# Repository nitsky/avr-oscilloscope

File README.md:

# avr-oscilloscope

Pushing the ATMega328 to its limit: A 150 ksps oscilloscope with edge triggering written in AVR C.

## ADC
The ADC is configured to operate in free running mode, which means it samples continuously and calls an interrupt when each new sample is ready, which is once every 13.5 ADC clock cycles. The top ADC clock speed for 8-bit resolution is 4MHz, a prescaler of 4 with a 16MHz processor clock. Here is the code that configures the ADC and then functions to start and stop it.

```c
void init_adc()
{
    cbi(ADCSRA, ADEN); // disable adc
    cbi(ADCSRA, ADSC); // stop conversion

    cbi(ADMUX, REFS1); // choose AVcc with external cap
    sbi(ADMUX, REFS0); // for adc voltage reference
    sbi(ADMUX, ADLAR); // left adjust adc readings for 8 bit
    ADMUX |= ( 0 & 0x07 ); // choose analog 0 pin

    sbi(ADCSRA, ADATE); // enable auto trigger of adc
    sbi(ADCSRA, ADIE); // enable adc interrupt

    cbi(ADCSRA, ADPS2); // set prescaler to 4
    sbi(ADCSRA, ADPS1); //
    cbi(ADCSRA, ADPS0); //

    cbi(ADCSRB, ACME); // choose AIN1 for comparator

    cbi(ADCSRB, ADTS2); // choose free running mode
    cbi(ADCSRB, ADTS1); // for auto trigger adc
    cbi(ADCSRB, ADTS0);
}

void start_adc()
{
    sbi( ADCSRA, ADEN );
    sbi( ADCSRA, ADSC );
}

void stop_adc()
{
    cbi( ADCSRA, ADEN );
    cbi( ADCSRA, ADSC );
}
```

## Comparator

The comparator is configured without an interrupt because the comparator's value is read in the ADC interrupt.

```c
void init_comparator(void)
{
    cbi( ACSR, ACD ); // turn on comparator
    cbi( ACSR, ACBG ); // choose digital pin 7 for comparator
    cbi( ACSR, ACIE ); // disable interrupt

    cbi( ACSR, ACIC ); // disable input capture interrupt
}
```

## ADC Interrupt

The ADC interrupt implements a circular buffer of 1024 8-bit samples. At each interrupt it checks if the comparator has detected the input voltage above the trigger level eight consecutive times, a simple noise filter, then sets the stop_index which the interrupt will freeze itself at when it hits it, which is the current index plus half the buffer length, so that the trigger event is always at the center of the circular buffer.

```c
ISR(ADC_vect)
{
    adc_data[adc_counter] = ADCH; // read adc
    if (freeze) {
        freeze = false;
        stop_index = -1;
    } else if (adc_counter == stop_index) {
        freeze = true;
    } else if ( comp == 0 && (ACSR & (1 << ACO)) && stop_index < 0) {
        stop_index = ((adc_counter + (ADC_BUFFER_SIZE >> 1) ) & 0x03FF);
    }
    adc_counter = (( adc_counter + 1 ) & 0x03FF); // increment adc counter
    comp = (comp << 1); // push next comparator value
    comp += (ACSR & (1 << ACO));
}
```

## Trigger Level DAC

The ATMega328 does not have a DAC built-in to set the trigger level, but you can cheat by using PWM with a low-pass filter. For PWM frequency 490 Hz, I used a 100 kΩ resistor and 1 uF capacitor you can get reasonable delay and ripple in the mV range. Below is the code to use PWM on PD3. After this setup function the duty cycle can be changed by modifying the OCR2B register.

```c
void init_pwm()
{
    setOutput(DDRD, PORTD3);
    sbi(TCCR2A, COM2B1);
    sbi(TCCR2A, WGM20);
    sbi(TCCR2B, CS22);
    OCR2B = 128;
}
```

## UART

The UART is configured for 115200 baud. Here's the code to initialize it and then functions to send and receive characters.

```
#define BAUD 115200
#include <util/setbaud.h>

void uart_init() {
    UBRR0H = UBRRH_VALUE;
    UBRR0L = UBRRL_VALUE;

#if USE_2X
    UCSR0A |= _BV(U2X0);
#else
    UCSR0A &= ~(_BV(U2X0));
#endif

    UCSR0C = _BV(UCSZ01) | _BV(UCSZ00); // 8 bit
    UCSR0B = _BV(RXEN0) | _BV(TXEN0); // enable rx and tx
}

void uart_putchar(char c) {
    loop_until_bit_is_set(UCSR0A, UDRE0); // wait until reg empty
    UDR0 = c;
}

char uart_getchar() {
    loop_until_bit_is_set(UCSR0A, RXC0); // wait for byte
    return UDR0;
}
```

## Signal Conditioning

Below is the input signal conditioning circuit. The ADC operates from 0V to 5V, so the circuit uses an op-amp to scale and offset an incoming signal from -10V to 10V to 0V to 5V. It does this with a divide by four voltage divider and then a voltage adder with a 2.5V input from a voltage divider. All resistors in the schematic are 10kΩ except for R11 with is 1 MΩ to make the scope appear as a high impedence to whatever circuit it is measuring.

## Results

[Watch Video](https://vimeo.com/80199995)

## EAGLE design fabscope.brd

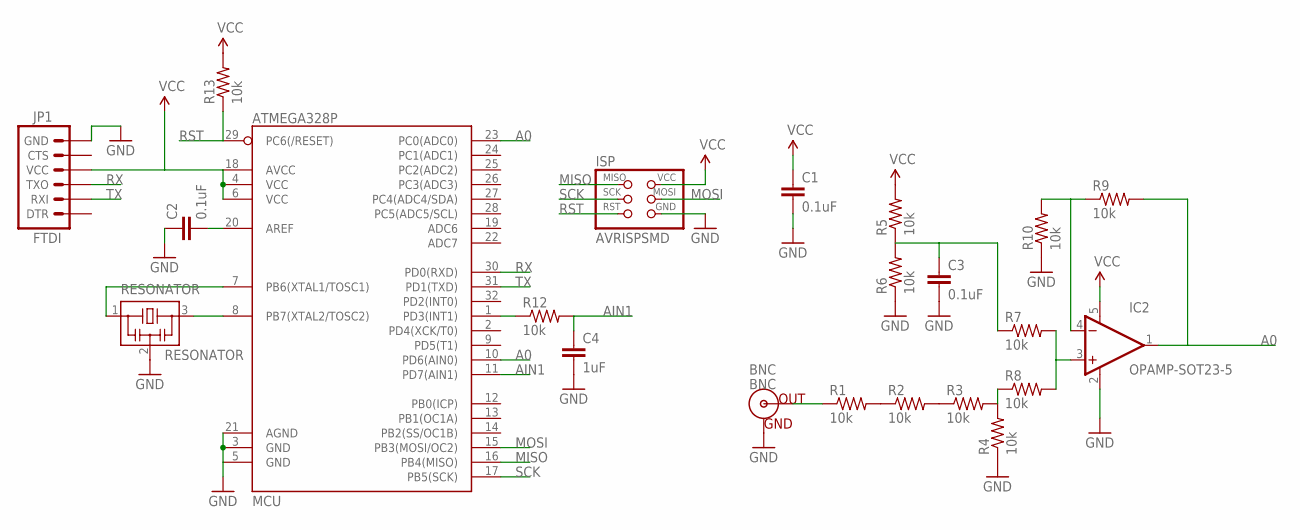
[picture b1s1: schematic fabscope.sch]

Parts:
BNC: BNC
C1, C2, C3: 0.1uF; C1206FAB
C4: 1uF; C1206FAB
IC2: OPAMP-SOT23-5; SOT23-5
ISP: AVRISPSMD; 2X3SMD
JP1: FTDI; FTDI-SMD
MCU: ATMEGA328P; TQFP32-08
R1, R2, R3, R4, R5, R6, R7, R8, R9, R10, R12, R13: 10k; R1206FAB
RESONATOR: RESONATOR; EFOBM

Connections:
A0: IC2.1 (OUT), MCU.10 (PD6(AIN0)), MCU.23 (PC0(ADC0)), R9.2
AIN1: C4.1, MCU.11 (PD7(AIN1)), R12.2
GND: BNC.GND, C1.2, C2.1, C3.2, C4.2, IC2.2 (V-), ISP.6 (GND), JP1.6 (GND), MCU.3 (GND), MCU.5 (GND), MCU.21 (AGND), R4.1, R6.1, R10.1, RESONATOR.2
MISO: ISP.1 (MISO), MCU.16 (PB4(MISO))
MOSI: ISP.4 (MOSI), MCU.15 (PB3(MOSI/OC2))
unnamed: MCU.7 (PB6(XTAL1/TOSC1)), RESONATOR.1
unnamed: MCU.8 (PB7(XTAL2/TOSC2)), RESONATOR.3
unnamed: BNC.S (OUT), R1.1
unnamed: C2.2, MCU.20 (AREF)
unnamed: R1.2, R2.1
unnamed: R2.2, R3.1
unnamed: R3.2, R4.2, R8.1
unnamed: C3.1, R5.1, R6.2, R7.1
unnamed: IC2.3 (+IN), R7.2, R8.2
unnamed: IC2.4 (-IN), R9.1, R10.2
unnamed: MCU.1 (PD3(INT1)), R12.1
RST: ISP.5 (RST), MCU.29 (PC6(/RESET)), R13.1
RX: JP1.3 (TXO), MCU.30 (PD0(RXD))
SCK: ISP.3 (SCK), MCU.17 (PB5(SCK))
TX: JP1.2 (RXI), MCU.31 (PD1(TXD))
VCC: C1.1, IC2.5 (V+), ISP.2 (VCC), JP1.4 (VCC), MCU.4 (VCC), MCU.6 (VCC), MCU.18 (AVCC), R5.2, R13.2

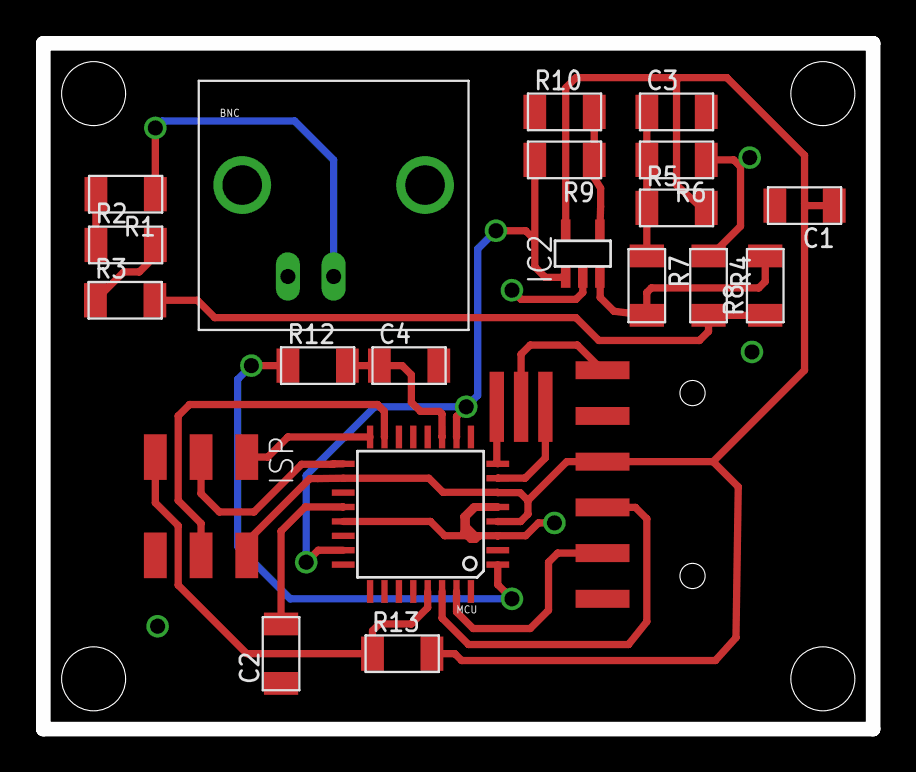
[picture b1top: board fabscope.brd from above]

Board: 2 copper layers, 46.1 x 38.1 mm, 22 parts (0 on the bottom side), 21 nets.

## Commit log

2013-11-24 initial import
2014-01-15 modified board and makefile
2014-01-15 removed old file
2014-01-15 fixes and fuses
2014-01-16 removed unused code
2014-04-02 rename
2016-01-25 add photos
2016-01-25 fix linkg
2016-01-25 move image

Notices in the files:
parts and their libraries:
SparkFun-Connectors: Licensing: CC v3.0 Share-Alike You are welcome to use this library for commercial purposes.
